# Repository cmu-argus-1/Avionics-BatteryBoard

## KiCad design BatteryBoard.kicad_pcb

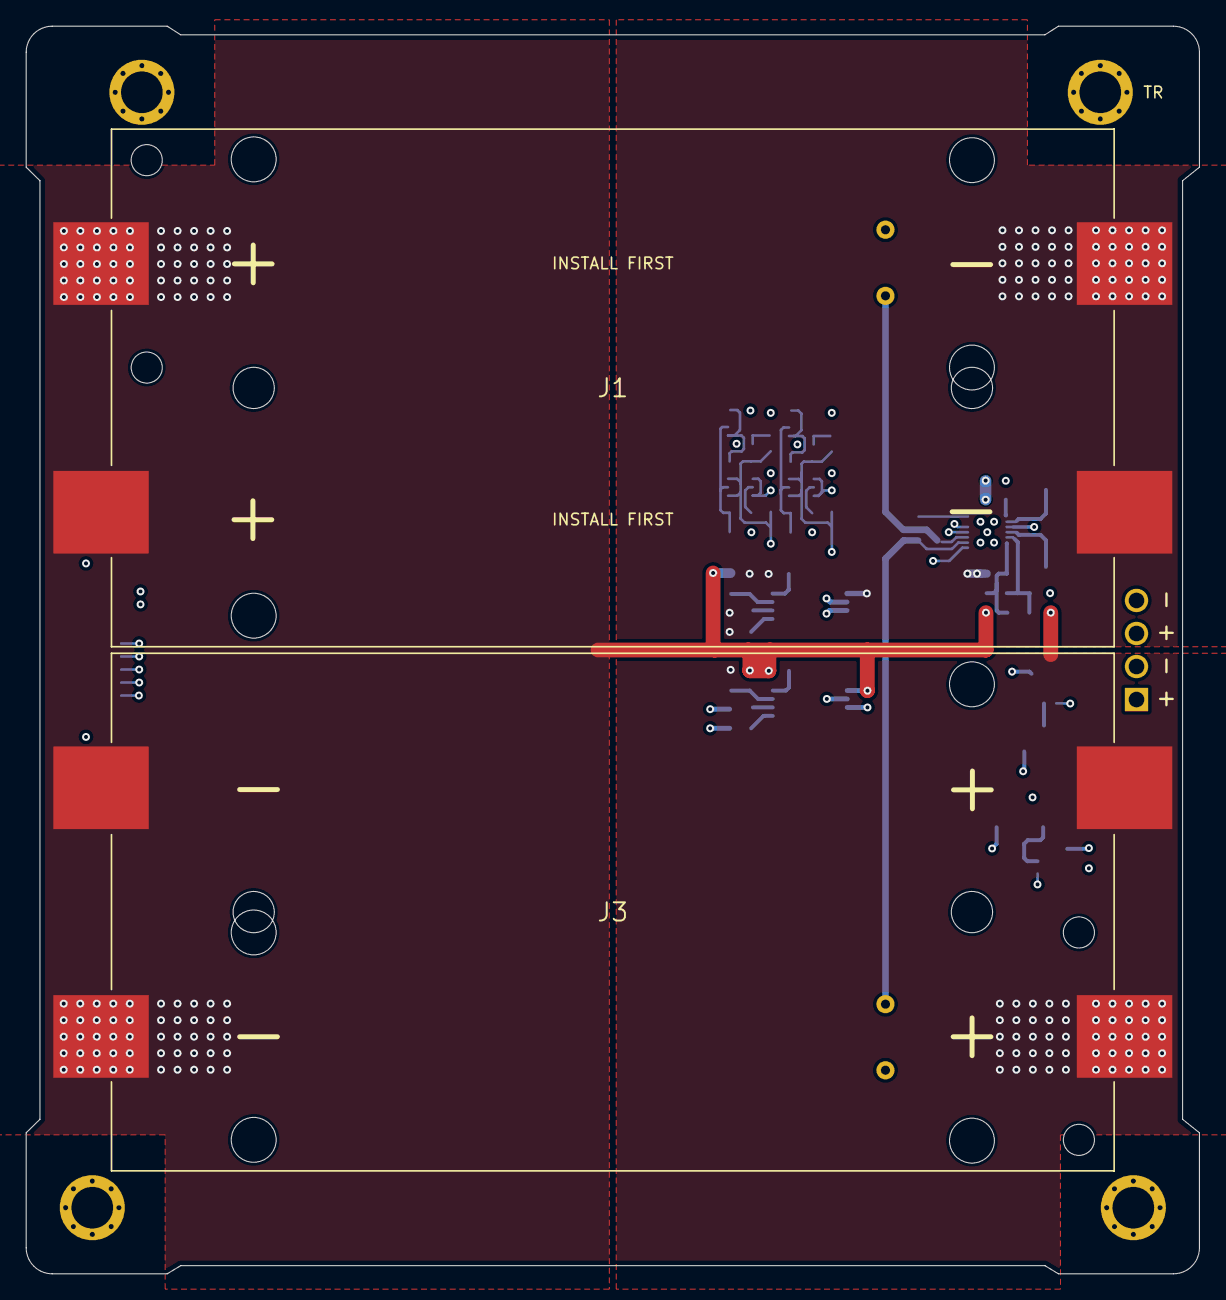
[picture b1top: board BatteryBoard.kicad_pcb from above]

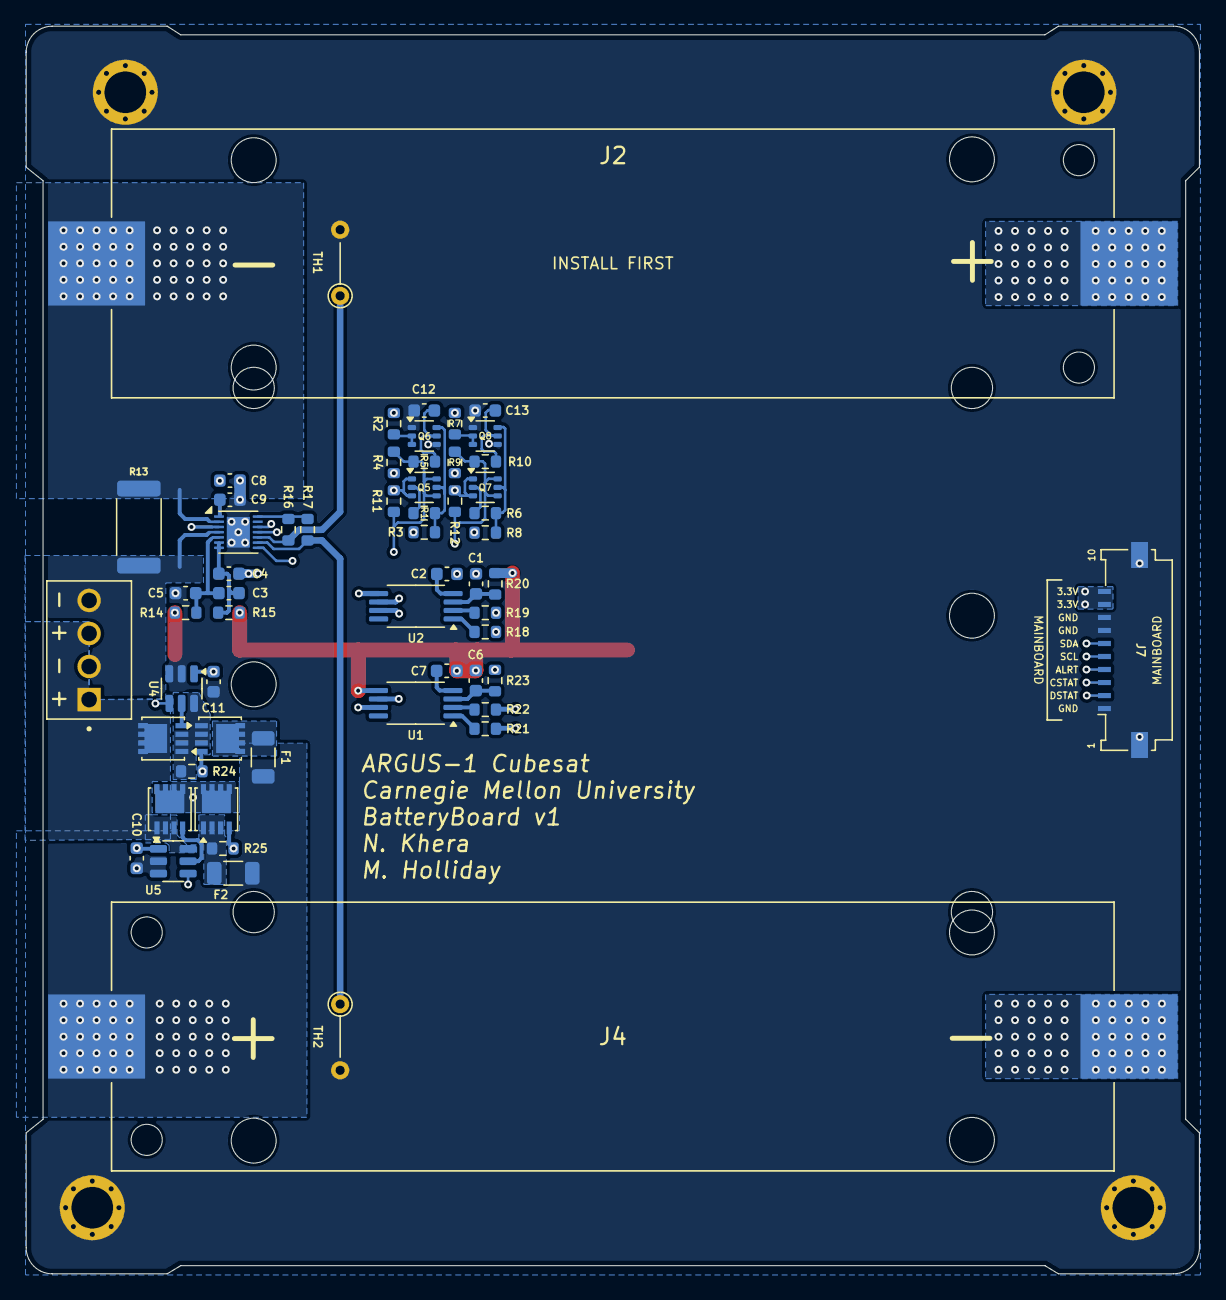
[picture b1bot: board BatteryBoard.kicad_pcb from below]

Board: 4 copper layers, 90.2 x 95.9 mm, 65 parts (60 on the bottom side), 47 nets.

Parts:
C1, C5, C6, C10, C11: 0.1uF; C_0603_1608Metric
C2, C7, C12, C13: 10nF; C_0603_1608Metric
C3, C4: 1nF; C_0603_1608Metric
C8, C9: 0.47uF; C_0603_1608Metric
F1, F2: Polyfuse_Small; R_1206_3216Metric
H1, H2, H3, H4: MountingHole_Pad; MountingHole
J1, J3: Keystone-1048; BAT_1048
J2, J4: Keystone-1042; Keystone_1042
J7: 200528-0100; Molex_200528-0100_1x10-1MP_P1.00mm_Horizontal
J8: 282834-4; TE_282834-4
Q1, Q2, Q3, Q4: Si7625DN; Vishay_PowerPAK_1212-8_Single
Q5, Q7: MBT2222ADW1T1; SOT-363_SC-70-6
Q6, Q8: NX3008NBKS; SOT-363_SC-70-6
R1, R6: 680R; R_0603_1608Metric
R2, R7, R24, R25: 100K; R_0603_1608Metric
R3, R4, R8, R9, R16, R17: 10K; R_0603_1608Metric
R5, R10: 200K; R_0603_1608Metric
R11, R12: DNI (0R); R_0603_1608Metric
R13: 10m; R_2512_6332Metric
R14: 10R; R_0603_1608Metric
R15: 100R; R_0603_1608Metric
R18, R19, R21, R22: 1K; R_0603_1608Metric
R20, R23: 470R; R_0603_1608Metric
TH1, TH2: 197-103LAG-A01; R_Axial_DIN0204_L3.6mm_D1.6mm_P5.08mm_Vertical
U1, U2: S-8209AAA-T8T1U; TSSOP-8_4.4x3mm_P0.65mm
U3: MAX17205; TDFN-14-1EP_3x3mm_P0.4mm_EP1.78x2.35mm
U4, U5: LTC4412xS6; TSOT-23-6

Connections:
+3V3: J7.9, J7.10, R2.1, R3.1, R4.1, R7.1, R8.1, R9.1
ALRT: J7.4, U3.8 (ALRT1)
B+: F1.1, F2.1, J3.2 (POS), J3.4 (POS), J4.2 (POS), R14.2, R23.1
B-: C1.2, C2.2, C4.2, J1.1 (NEG), J1.3 (NEG), J2.1 (NEG), R13.2, R18.1, R19.1, U2.5 (VSS), U3.2 (CSP)
BM: C6.2, C7.2, J1.2 (POS), J1.4 (POS), J2.2 (POS), J3.1 (NEG), J3.3 (NEG), J4.1 (NEG), R15.2, R20.1, U1.5 (VSS)
CSTAT: J7.3, U4.4 (STAT)
DSTAT: J7.2, U5.4 (STAT)
GND: C5.2, C8.2, C9.2, C10.2, C11.2, C12.2, C13.2, H1.1, H2.1, H3.1, H4.1, J7.1, J7.7, J7.8, J7.MP (MountPin), Q6.1 (S2), Q6.4 (S1), Q8.1 (S2), Q8.4 (S1), TH1.2, TH2.2, U3.15 (GND), U4.2 (GND), U4.3 (CTL), U5.2 (GND), U5.3 (CTL)
unnamed: F2.2, Q3.1 (S), Q3.2 (S), Q3.3 (S), R25.2
unnamed: F1.2, Q1.5 (D)
unnamed: Q1.4 (G), R24.2, U1.7 (CO)
unnamed: Q2.4 (G), U4.5 (GATE)
unnamed: C10.1, Q3.5 (D), Q4.5 (D), U5.1 (VIN)
unnamed: Q3.4 (G), R25.1, U1.6 (DO)
unnamed: Q4.4 (G), U5.5 (GATE)
unnamed: Q5.2 (B1), R1.1
unnamed: Q5.5 (B2), Q6.6 (D1), R1.2, R3.2
unnamed: Q6.2 (G2), Q6.3 (D2), R2.2
unnamed: C12.1, Q6.5 (G1), R5.2
unnamed: Q7.2 (B1), R6.1
unnamed: Q7.5 (B2), Q8.6 (D1), R6.2, R8.2
unnamed: Q8.2 (G2), Q8.3 (D2), R7.2
unnamed: C13.1, Q8.5 (G1), R10.2
unnamed: C7.1, U1.4 (CDT)
unnamed: R21.2, U1.1 (CTLC)
unnamed: R22.2, U1.2 (CTLD)
unnamed: C6.1, R23.2, U1.3 (VDD)
unnamed: C2.1, U2.4 (CDT)
unnamed: R21.1, U2.7 (CO)
unnamed: R18.2, U2.1 (CTLC)
unnamed: R19.2, U2.2 (CTLD)
unnamed: R22.1, U2.6 (DO)
unnamed: C1.1, R20.2, U2.3 (VDD)
unnamed: R17.2, TH2.1, U3.9 (AIN1)
unnamed: R16.2, TH1.1, U3.10 (AIN2)
unnamed: C3.2, C4.1, R15.1, U3.6 (CELL2), U3.7 (CELL1)
unnamed: C8.1, U3.3 (REG2)
unnamed: C9.1, U3.1 (REG3)
unnamed: R16.1, R17.1, U3.14 (THRM)
unnamed: C3.1, C5.1, R14.1, U3.5 (VBATT)
unnamed: Q1.1 (S), Q1.2 (S), Q1.3 (S), Q2.1 (S), Q2.2 (S), Q2.3 (S), R24.1, U4.6 (SENSE)
PACK+: C11.1, J8.1, J8.3, Q2.5 (D), Q4.1 (S), Q4.2 (S), Q4.3 (S), U4.1 (VIN), U5.6 (SENSE)
PACK-: J8.2, J8.4, R13.1, U3.4 (CSN)
SCL: J7.5, Q5.1 (E1), Q5.3 (C2), R11.2
SCL_Fuel: Q5.4 (E2), Q5.6 (C1), R4.2, R5.1, R11.1, U3.11 (SCL)
SDA: J7.6, Q7.1 (E1), Q7.3 (C2), R12.2
SDA_Fuel: Q7.4 (E2), Q7.6 (C1), R9.2, R10.1, R12.1, U3.12 (SDA)

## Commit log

2024-06-16 Upload .gitignore
2024-06-22 Upload Files
2024-06-22 Finish v1 schematic
2024-06-22 Cleanup component designators
2024-06-28 Complete layout
2024-07-02 Moved things idek
2024-07-19 v1 Final
2024-09-10 Relabeled I2C nets for accuracy
